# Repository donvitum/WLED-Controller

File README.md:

# WLED-Controller
WLED Controller with DHT22 Connector for 3D Printer Case

For WS281x and APA LED Stribes

Aktuell noch ungetestet. :) Sobald die Platinen ankommen gibt es hier ein Update.

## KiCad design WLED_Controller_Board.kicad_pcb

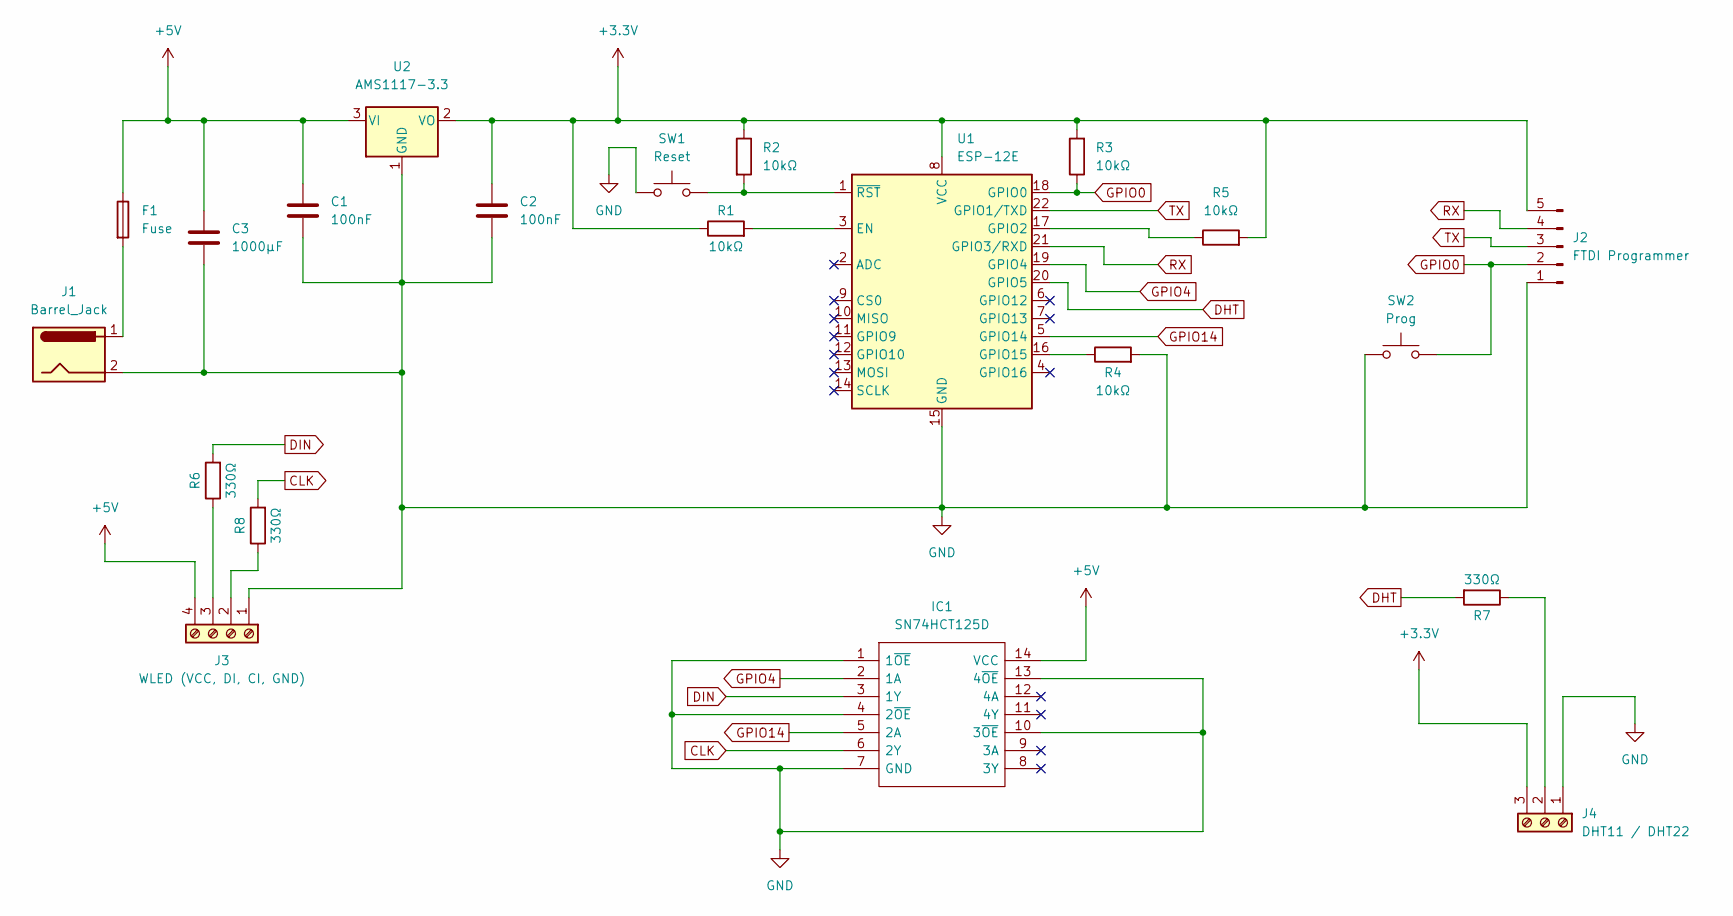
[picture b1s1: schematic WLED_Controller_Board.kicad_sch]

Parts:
C1, C2: 100nF; C_0603_1608Metric_Pad1.08x0.95mm_HandSolder
C3: 1000μF; C_Radial_D10.0mm_H20.0mm_P5.00mm
F1: Fuse; Fuseholder_Littelfuse_100_series_5x20mm
IC1: SN74HCT125D; SOIC127P600X175-14N; Manufacturer_Part_Number SN74HCT125D; Mouser Part Number 595-SN74HCT125D
J1: Barrel_Jack; BarrelJack_Wuerth_6941xx301002
J2: FTDI Programmer; PinHeader_1x05_P2.54mm_Horizontal
J3: WLED (VCC, DI, CI, GND); TerminalBlock_Phoenix_PT-1,5-4-3.5-H_1x04_P3.50mm_Horizontal
J4: DHT11 / DHT22; TerminalBlock_Phoenix_PT-1,5-3-3.5-H_1x03_P3.50mm_Horizontal
R1, R2, R3, R4, R5: 10kΩ; R_0603_1608Metric_Pad0.98x0.95mm_HandSolder
R6, R7, R8: 330Ω; R_0603_1608Metric_Pad0.98x0.95mm_HandSolder
SW1: Reset; SW_SPST_CK_RS282G05A3
SW2: Prog; SW_SPST_CK_RS282G05A3
U1: ESP-12E
U2: AMS1117-3.3; SOT-223-3_TabPin2

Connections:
+3V3: C2.1, J2.5, J4.3, R1.1, R2.1, R3.2, R5.2, U1.8 (VCC), U2.2 (VO)
+5V: C1.1, C3.1, F1.1, IC1.14 (VCC), J3.4, U2.3 (VI)
CLK: IC1.6 (2Y), R8.2
DHT: R7.2, U1.20 (GPIO5)
DIN: IC1.3 (1Y), R6.2
GND: C1.2, C2.2, C3.2, IC1.1 (1~OE), IC1.4 (2~OE), IC1.7 (GND), IC1.10 (3~OE), IC1.13 (4~OE), J1.2, J2.1, J3.1, J4.1, R4.2, SW1.1, SW2.1, U1.15 (GND), U2.1 (GND)
GPIO0: J2.2, R3.1, SW2.2, U1.18 (GPIO0)
GPIO4: IC1.2 (1A), U1.19 (GPIO4)
GPIO14: IC1.5 (2A), U1.5 (GPIO14)
unnamed: F1.2, J1.1
unnamed: J3.2, R8.1
unnamed: J3.3, R6.1
unnamed: J4.2, R7.1
unnamed: R1.2, U1.3 (EN)
unnamed: R2.2, SW1.2, U1.1 (~RST)
unnamed: R4.1, U1.16 (GPIO15)
unnamed: R5.1, U1.17 (GPIO2)
RX: J2.4, U1.21 (GPIO3/RXD)
TX: J2.3, U1.22 (GPIO1/TXD)

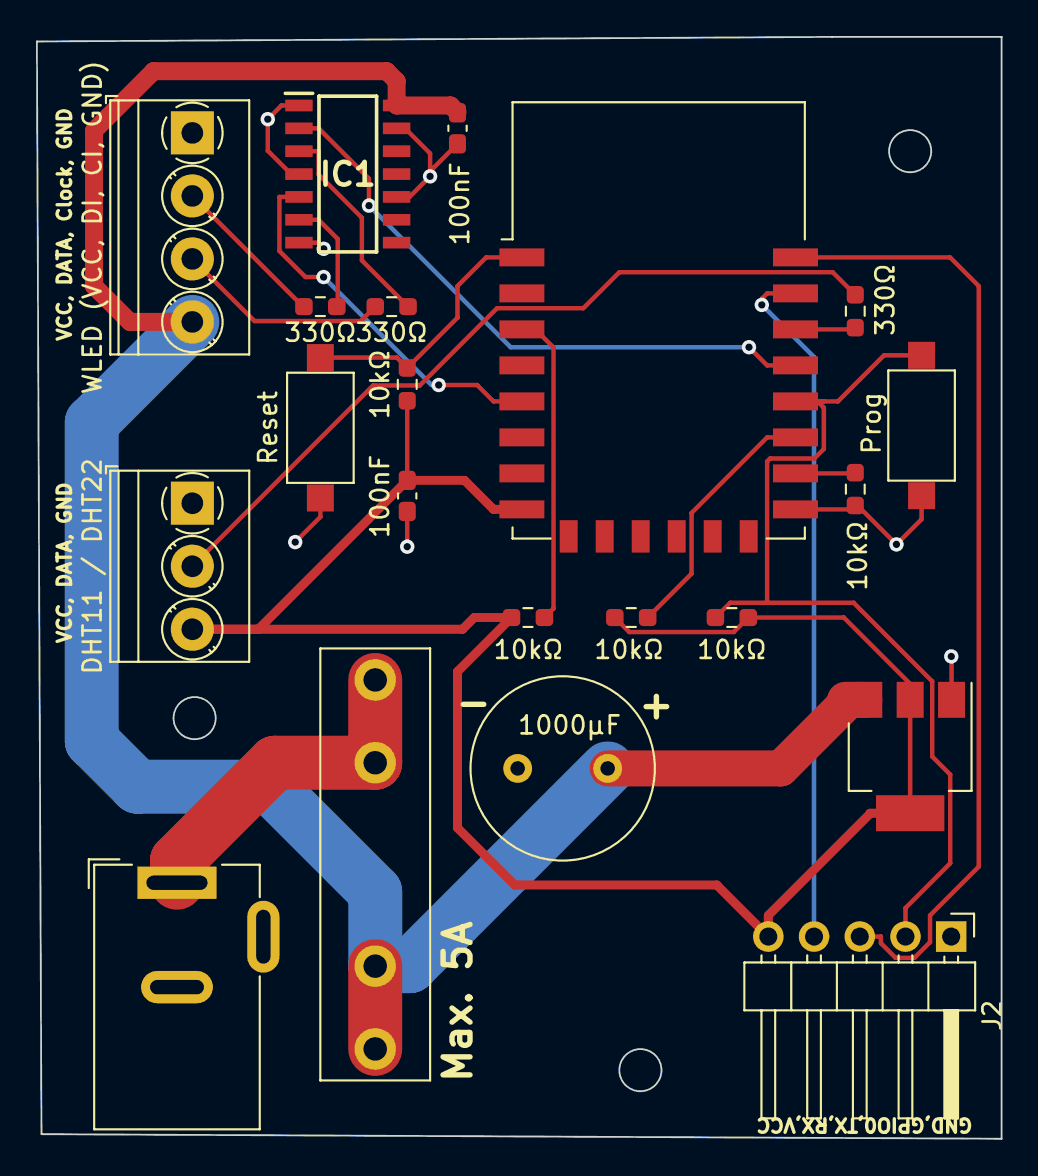
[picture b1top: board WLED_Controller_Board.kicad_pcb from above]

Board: 2 copper layers, 53.6 x 61.2 mm, 21 parts (0 on the bottom side), 19 nets.

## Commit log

2021-12-13 Add files via upload
    Change DHT VCC to 3.3V
